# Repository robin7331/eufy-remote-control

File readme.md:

# Eufy Make Remote Control Button Box

This repository contains both the **software** and **hardware** files for the Eufy Make Remote Control Button Box project.

## Overview

- **Hardware**: Kicad PCB designs
- **Software**: MicroPython code for the RP2040 Stamp

## Connectivity

The button box is designed to connect to an **MQTT broker**.

---

For details, see the `hardware/` and `software/` folders.

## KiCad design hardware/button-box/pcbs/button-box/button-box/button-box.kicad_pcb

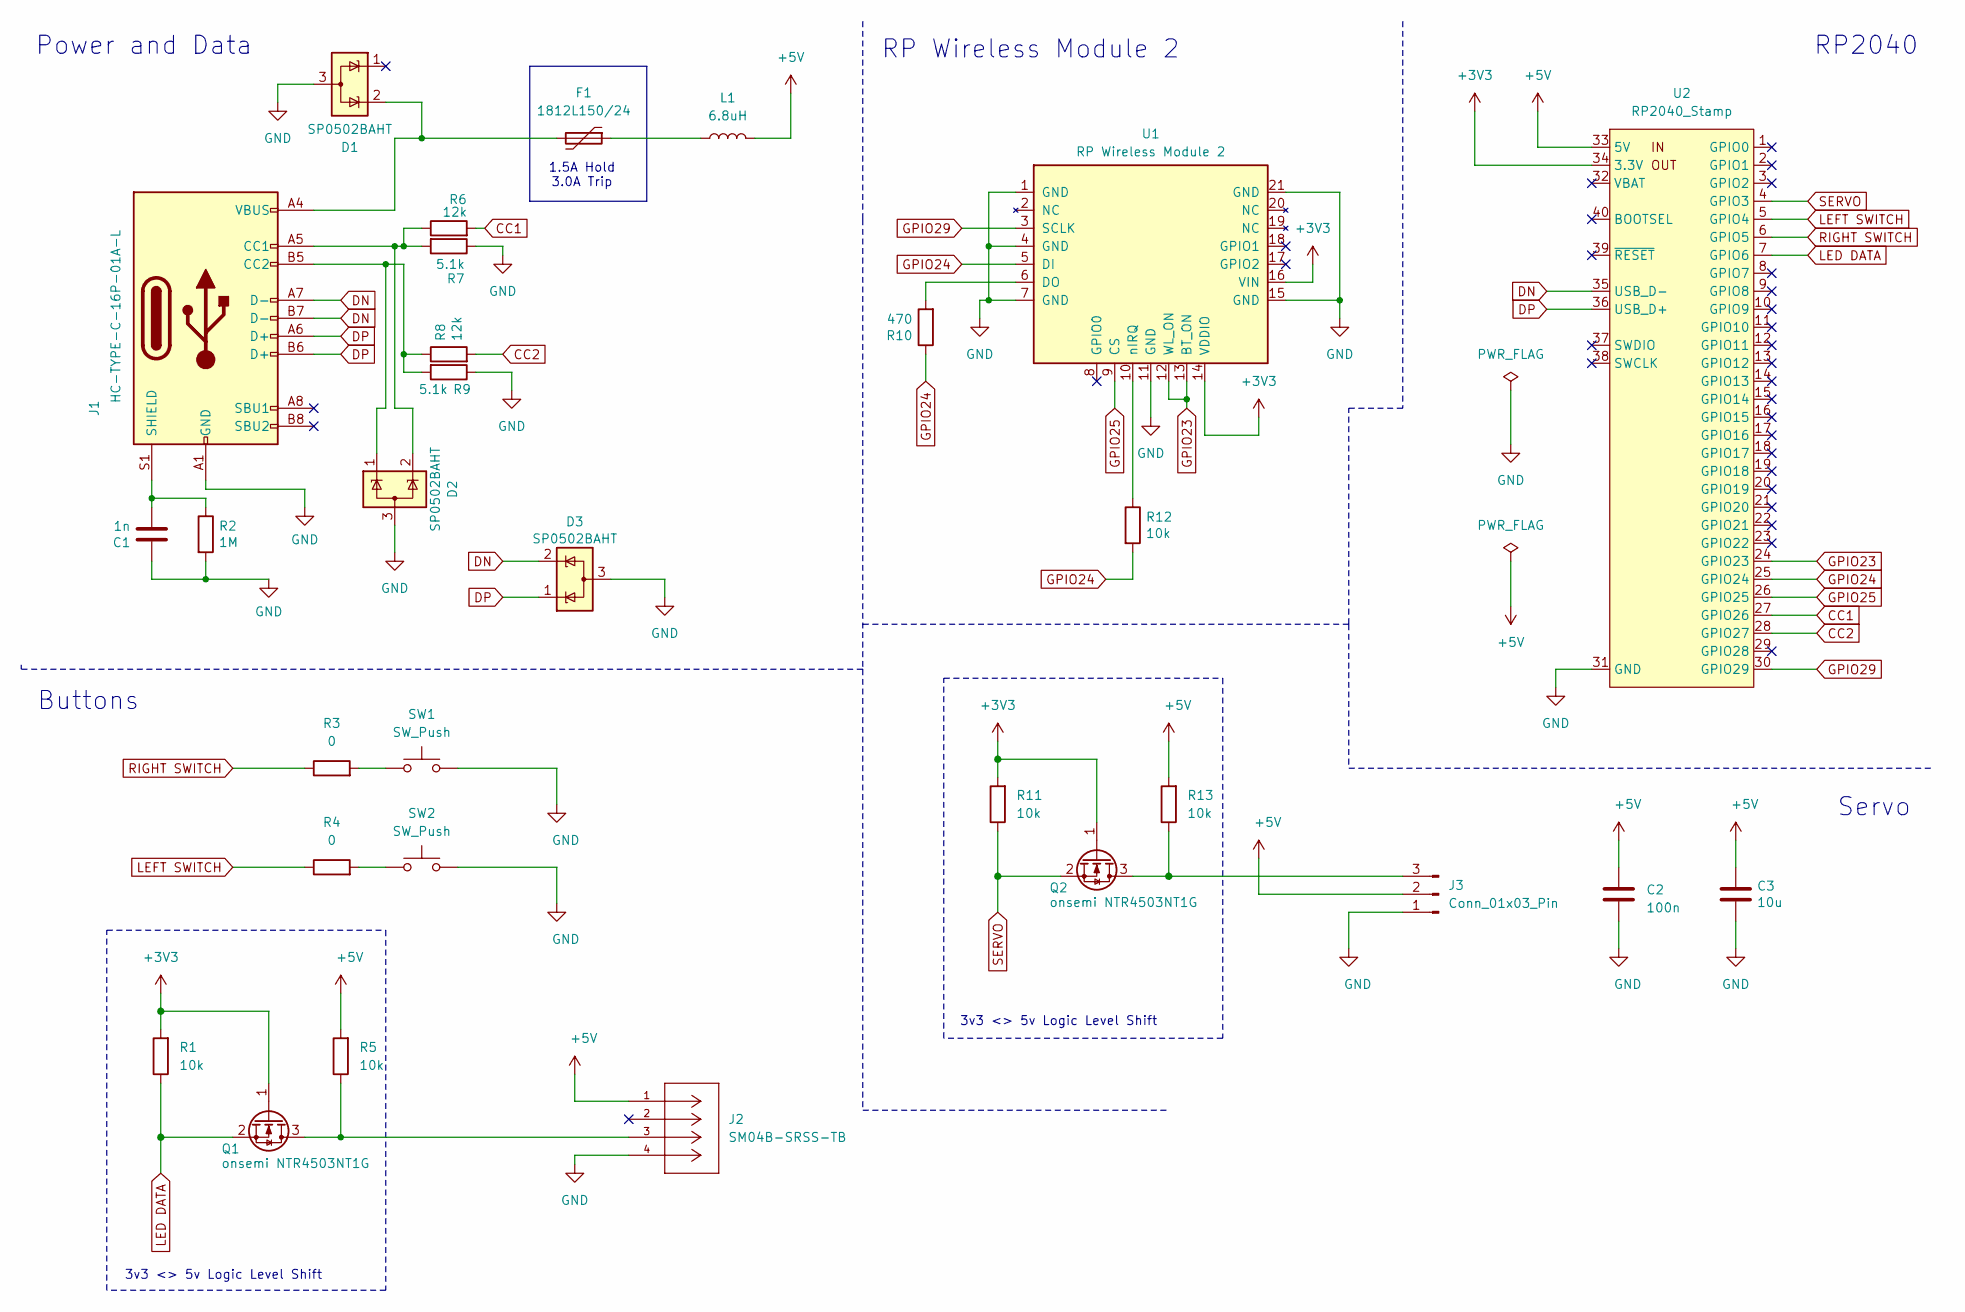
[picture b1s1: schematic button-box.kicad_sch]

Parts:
C1: 1n; C_0603_1608Metric; MPN 1n 0603
C2: 100n; C_0603_1608Metric; MPN 100n 0603
C3: 10u; C_0805_2012Metric
D1, D2, D3: SP0502BAHT; SOT-23; MPN SP0502BAHT
F1: 1812L150/24; Fuse_1812_4532Metric; MPN 1812L075PR
J1: HC-TYPE-C-16P-01A-L; USB_C_Purple
J2: SM04B-SRSS-TB; CONN_SM04B-SRSS-TB_JST; MANUFACTURER_PART_NUMBER SM04B-SRSS-TB
J3: Conn_01x03_Pin; PinHeader_1x03_P2.54mm_Horizontal
L1: 6.8uH; L_TDK_SLF7032; MPN SLF7032T-6R8M1R6-2-PF
Q1, Q2: onsemi NTR4503NT1G; SOT-23; MPN NTR4503NT1G
R1, R5, R11, R13: 10k; R_0603_1608Metric; MPN 10k 0603
R2: 1M; R_0603_1608Metric; MPN 1M 0603
R3, R4: 0; C_0603_1608Metric
R6, R8: 12k; R_0603_1608Metric; MPN 1M 0603
R7: 5.1k; R_0603_1608Metric; MPN 5.1k 0402
R9: 5.1k; R_0603_1608Metric; MPN 5.1k 0603
R10: 470; R_0603_1608Metric; MPN 1M 0603
R12: 10k; R_0603_1608Metric; MPN 1M 0603
SW1, SW2: SW_Push; SW_MX_LowProfile_THT
U1: RP Wireless Module 2; rpi_rmc20452t
U2: RP2040_Stamp; RP2xxx_Stamp_SMD

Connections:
+3V3: Q1.1 (G), Q2.1 (G), R1.2, R11.2, U1.14 (VDDIO), U1.16 (VIN), U2.34 (3.3V)
+5V: C2.1, C3.1, J2.1, J3.2, L1.2, R5.2, R13.2, U2.33 (5V)
CC1: R6.2, U2.27 (GPIO26)
CC2: R8.2, U2.28 (GPIO27)
DN: D3.2 (K), J1.A7 (D-), J1.B7 (D-), U2.35 (USB_D-)
DP: D3.1 (K), J1.A6 (D+), J1.B6 (D+), U2.36 (USB_D+)
GND: C1.1, C2.2, C3.2, D1.3 (A), D2.3 (A), D3.3 (A), J1.A1 (GND), J1.A12 (GND), J1.B1 (GND), J1.B12 (GND), J2.4, J3.1, R2.2, R7.1, R9.1, SW1.2, SW2.2, U1.1 (GND), U1.4 (GND), U1.7 (GND), U1.11 (GND), U1.15 (GND), U1.21 (GND), U2.31 (GND)
GPIO23: U1.12 (WL_ON), U1.13 (BT_ON), U2.24 (GPIO23)
GPIO24: R10.1, R12.2, U1.5 (DI), U2.25 (GPIO24)
GPIO25: U1.9 (CS), U2.26 (GPIO25)
GPIO29: U1.3 (SCLK), U2.30 (GPIO29)
LED DATA: Q1.2 (S), R1.1, U2.7 (GPIO6)
LEFT SWITCH: R4.1, U2.5 (GPIO4)
unnamed: D1.2 (K), F1.2, J1.A4 (VBUS), J1.A9 (VBUS), J1.B4 (VBUS), J1.B9 (VBUS)
unnamed: F1.1, L1.1
unnamed: D2.2 (K), J1.A5 (CC1), R6.1, R7.2
unnamed: D2.1 (K), J1.B5 (CC2), R8.1, R9.2
unnamed: C1.2, J1.S1 (SHIELD), R2.1
unnamed: J3.3, Q2.3 (D), R13.1
unnamed: J2.3, Q1.3 (D), R5.1
unnamed: R3.2, SW1.1
unnamed: R4.2, SW2.1
unnamed: R10.2, U1.6 (DO)
unnamed: R12.1, U1.10 (nIRQ)
RIGHT SWITCH: R3.1, U2.6 (GPIO5)
SERVO: Q2.2 (S), R11.1, U2.4 (GPIO3)

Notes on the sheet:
3v3 <> 5v Logic Level Shift
RP2040
Power and Data
Servo
Buttons
RP Wireless Module 2
1.5A Hold 3.0A Trip

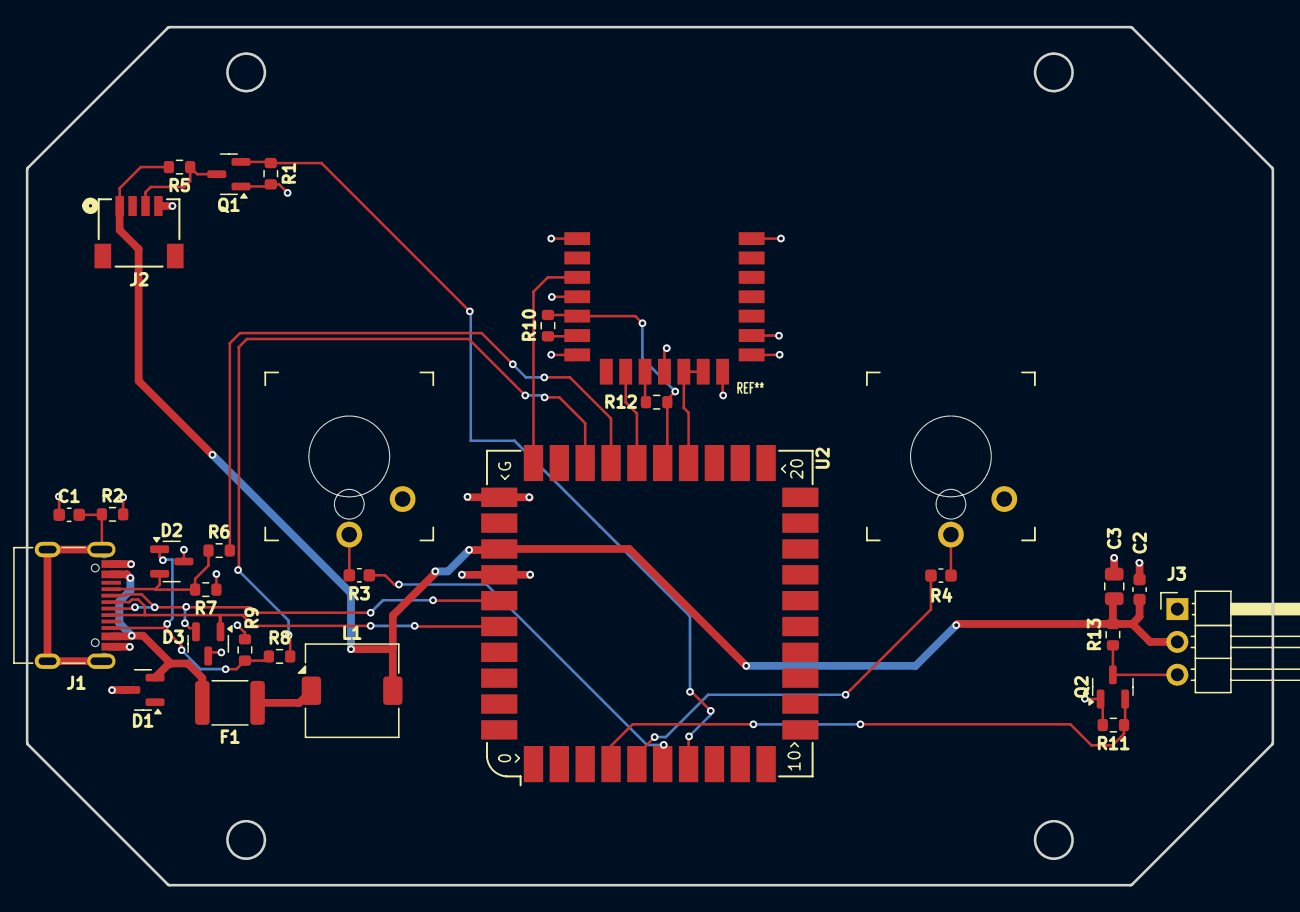
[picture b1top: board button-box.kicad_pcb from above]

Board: 4 copper layers, 96.4 x 66.4 mm, 30 parts (0 on the bottom side), 26 nets.

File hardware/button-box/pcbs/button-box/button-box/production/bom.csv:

Designator,Footprint,Quantity,Value,LCSC Part #
C1,0603,1,1n,1n 0603
C2,0603,1,100n,100n 0603
C3,0805,1,10u,
"D1, D2, D3",SOT-23,3,SP0502BAHT,SP0502BAHT
F1,1812,1,1812L150/24,1812L075PR
J1,USB_C_Purple,1,HC-TYPE-C-16P-01A-L,
J2,CONN_SM04B-SRSS-TB_JST,1,SM04B-SRSS-TB,
J3,PinHeader_1x03_P2.54mm_Horizontal,1,Conn_01x03_Pin,
L1,L_TDK_SLF7032,1,6.8uH,SLF7032T-6R8M1R6-2-PF
"Q1, Q2",SOT-23,2,onsemi NTR4503NT1G,NTR4503NT1G
"R1, R11, R13, R5",0603,4,10k,10k 0603
R10,0603,1,470,1M 0603
R12,0603,1,10k,1M 0603
R2,0603,1,1M,1M 0603
"R3, R4",0603,2,0,
"R6, R8",0603,2,12k,1M 0603
R7,0603,1,5.1k,5.1k 0402
R9,0603,1,5.1k,5.1k 0603
"SW1, SW2",SW_MX_LowProfile_THT,2,SW_Push,
U1,rpi_rmc20452t,1,RP Wireless Module 2,
U2,RP2xxx_Stamp_SMD,1,RP2040_Stamp,

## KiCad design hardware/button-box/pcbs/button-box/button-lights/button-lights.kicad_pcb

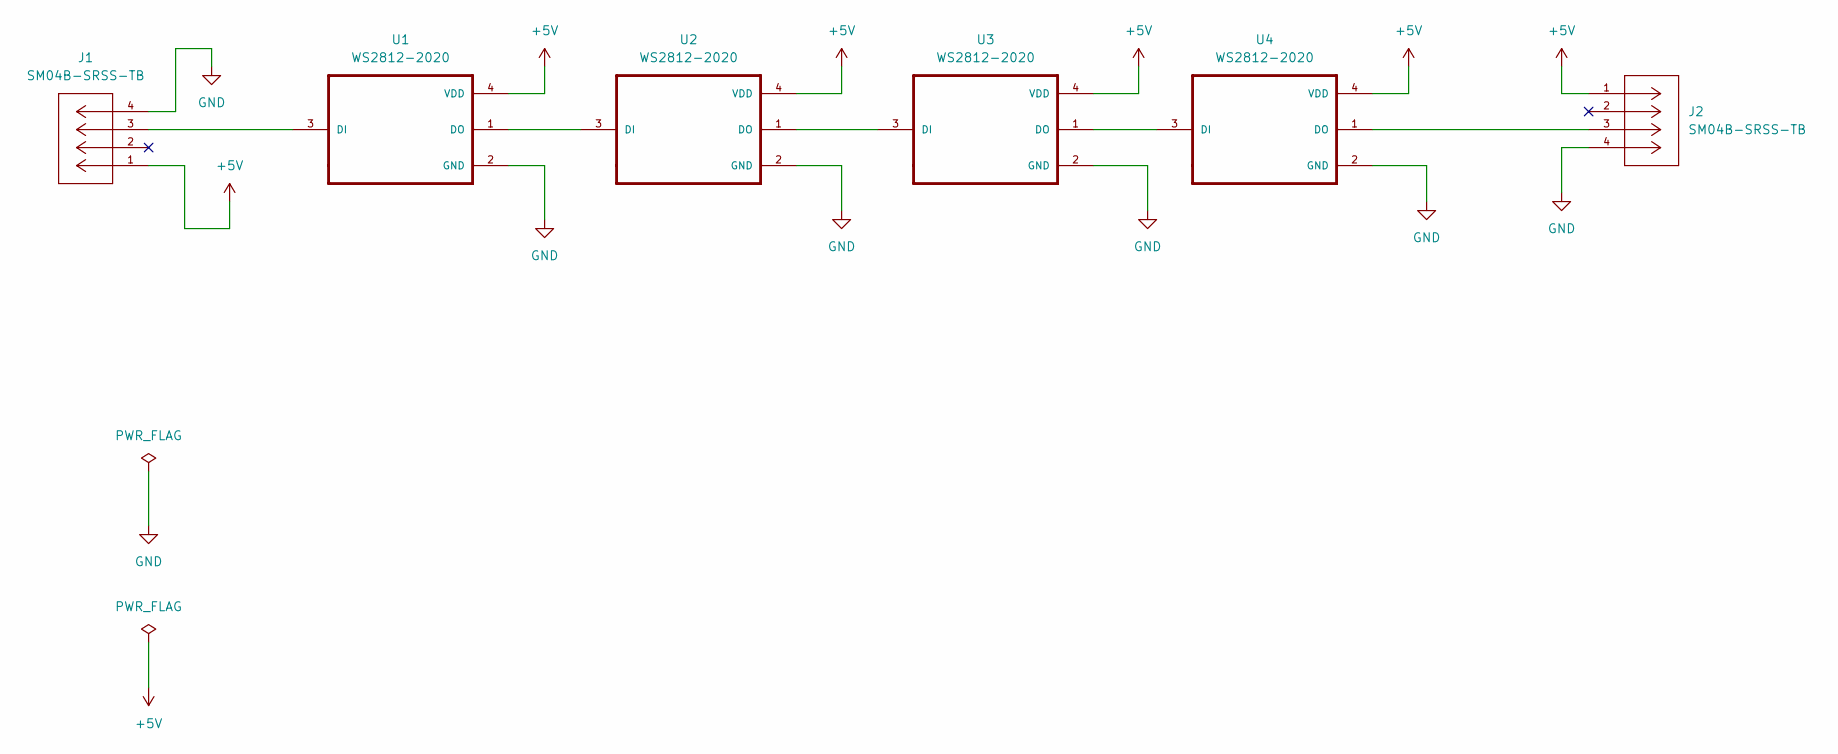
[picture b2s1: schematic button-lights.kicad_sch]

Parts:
J1, J2: SM04B-SRSS-TB; CONN_SM04B-SRSS-TB_JST; MANUFACTURER_PART_NUMBER SM04B-SRSS-TB
U1, U2, U3, U4: WS2812-2020; LED_WS2812-2020

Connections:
+5V: J1.1, J2.1, U1.4 (VDD), U2.4 (VDD), U3.4 (VDD), U4.4 (VDD)
GND: J1.4, J2.4, U1.2 (GND), U2.2 (GND), U3.2 (GND), U4.2 (GND)
unnamed: J1.3, U1.3 (DI)
unnamed: U1.1 (DO), U2.3 (DI)
unnamed: U2.1 (DO), U3.3 (DI)
unnamed: U3.1 (DO), U4.3 (DI)
unnamed: J2.3, U4.1 (DO)

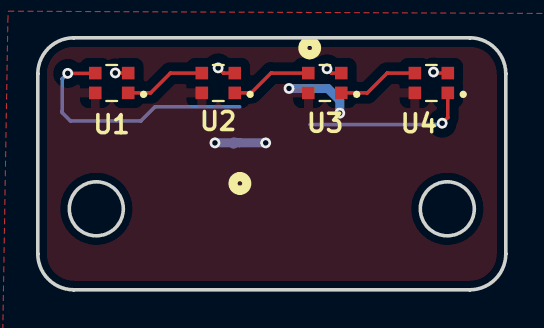
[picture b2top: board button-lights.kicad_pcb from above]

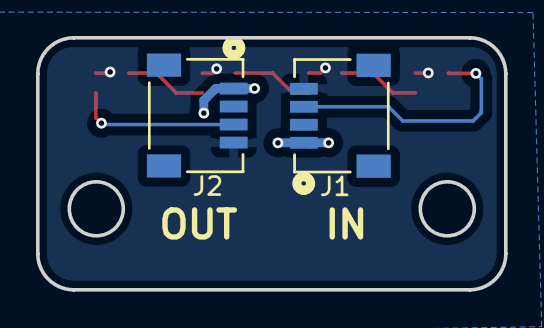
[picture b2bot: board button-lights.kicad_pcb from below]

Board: 2 copper layers, 26.0 x 14.0 mm, 6 parts (2 on the bottom side), 7 nets.

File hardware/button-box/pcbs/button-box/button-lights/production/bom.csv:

Designator,Footprint,Quantity,Value,LCSC Part #
"J1, J2",CONN_SM04B-SRSS-TB_JST,2,SM04B-SRSS-TB,
"U1, U2, U3, U4",LED_WS2812-2020,4,WS2812-2020,

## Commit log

2025-08-29 initial
2025-09-03 pcb ordered
2025-09-11 final :D
2025-09-11 add ignore
2025-09-11 Initial software
2025-09-11 Generate Bom
2025-09-19 generated bom
2025-09-19 kicad
2025-09-19 Fix extended angle
2025-09-19 Add readme

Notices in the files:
parts and their libraries:
COPYRIGHT: Copyright (C) 2024 Ultra Librarian. All rights reserved.
